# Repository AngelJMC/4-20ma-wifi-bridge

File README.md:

# 4-20ma-wifi-bridge
IoT device to provide communication between 4-20mA sensors and cloud services. Powered by an ESP32, it allows a wireless connection via WIFI, the communication with the server is done through the MQTT protocol. The device has a user-friendly web configuration interface, which allows to manage the wifi connection, the connection with the MQTT broker as well as the calibration of the 4-20mA acquisition system. 

## Features
### Hardware
 * 5-24v Power supply.
 * 1 Input 4-20 mA.
 * 2 Relays to control loads up to 1A at 24DVC or 0.5A at 125VAC.
 * WIFI 802.11 b/g/n (2.4 GHz), up to 150 Mbps.

## Get the source code
Download repository and update submodules:

```
$ git clone https://github.com/AngelJMC/4-20ma-wifi-bridge.git
```

### Directory Structure

    .
    ├── docs          # Documentation files
    ├── firmware      # FW source code (Visual Studio Code)
    ├── hardware      # HW design files (Kicad)

## Firmware

If you want to modify the source code or program your devices, it is highly recommended to use Visual Studio Code and the Platformio plugin. Just open the "firmware" directory with Visual Studio Code and the whole project will be ready for use.

### Load firmware 

 1. Build and Upload Filesystem Image.
 2. Build and Upload program code.

## Configuration Process

 1. Build and Upload Filesystem Image to your ESP32
 2. Build and Upload program code.
 3. Connect mobile or PC with hotspot: Logger_4-20mA_XXXX. Password: Kmf5cyJUWw
 4. Go to web browser and hit 192.168.4.1. Use the credential supervisor/fEVcCQxig to enter.
 5. Go to Network section and scan for your wifi network, write password and static network configuration if you want, hit apply.
 6. Go to Service section give necessary server credential for MQTT and set the pub/sub topic names.
 7. Go to Other section if you need calibrate the 4-20mA acquisition electronic.

## Configuration Web

## Library Used

* ESp32_arduino :- https://github.com/espressif/arduino-esp32
* ESPAsyncWebServer:- https://github.com/me-no-dev/ESPAsyncWebServer
* AsyncTCP:- https://github.com/me-no-dev/AsyncTCP
* esp32 SPIFF File system :- https://github.com/me-no-dev/arduino-esp32fs-plugin

The configuration web page is based on the work of @futechiot https://github.com/futechiot/Configuration-webpage-esp32

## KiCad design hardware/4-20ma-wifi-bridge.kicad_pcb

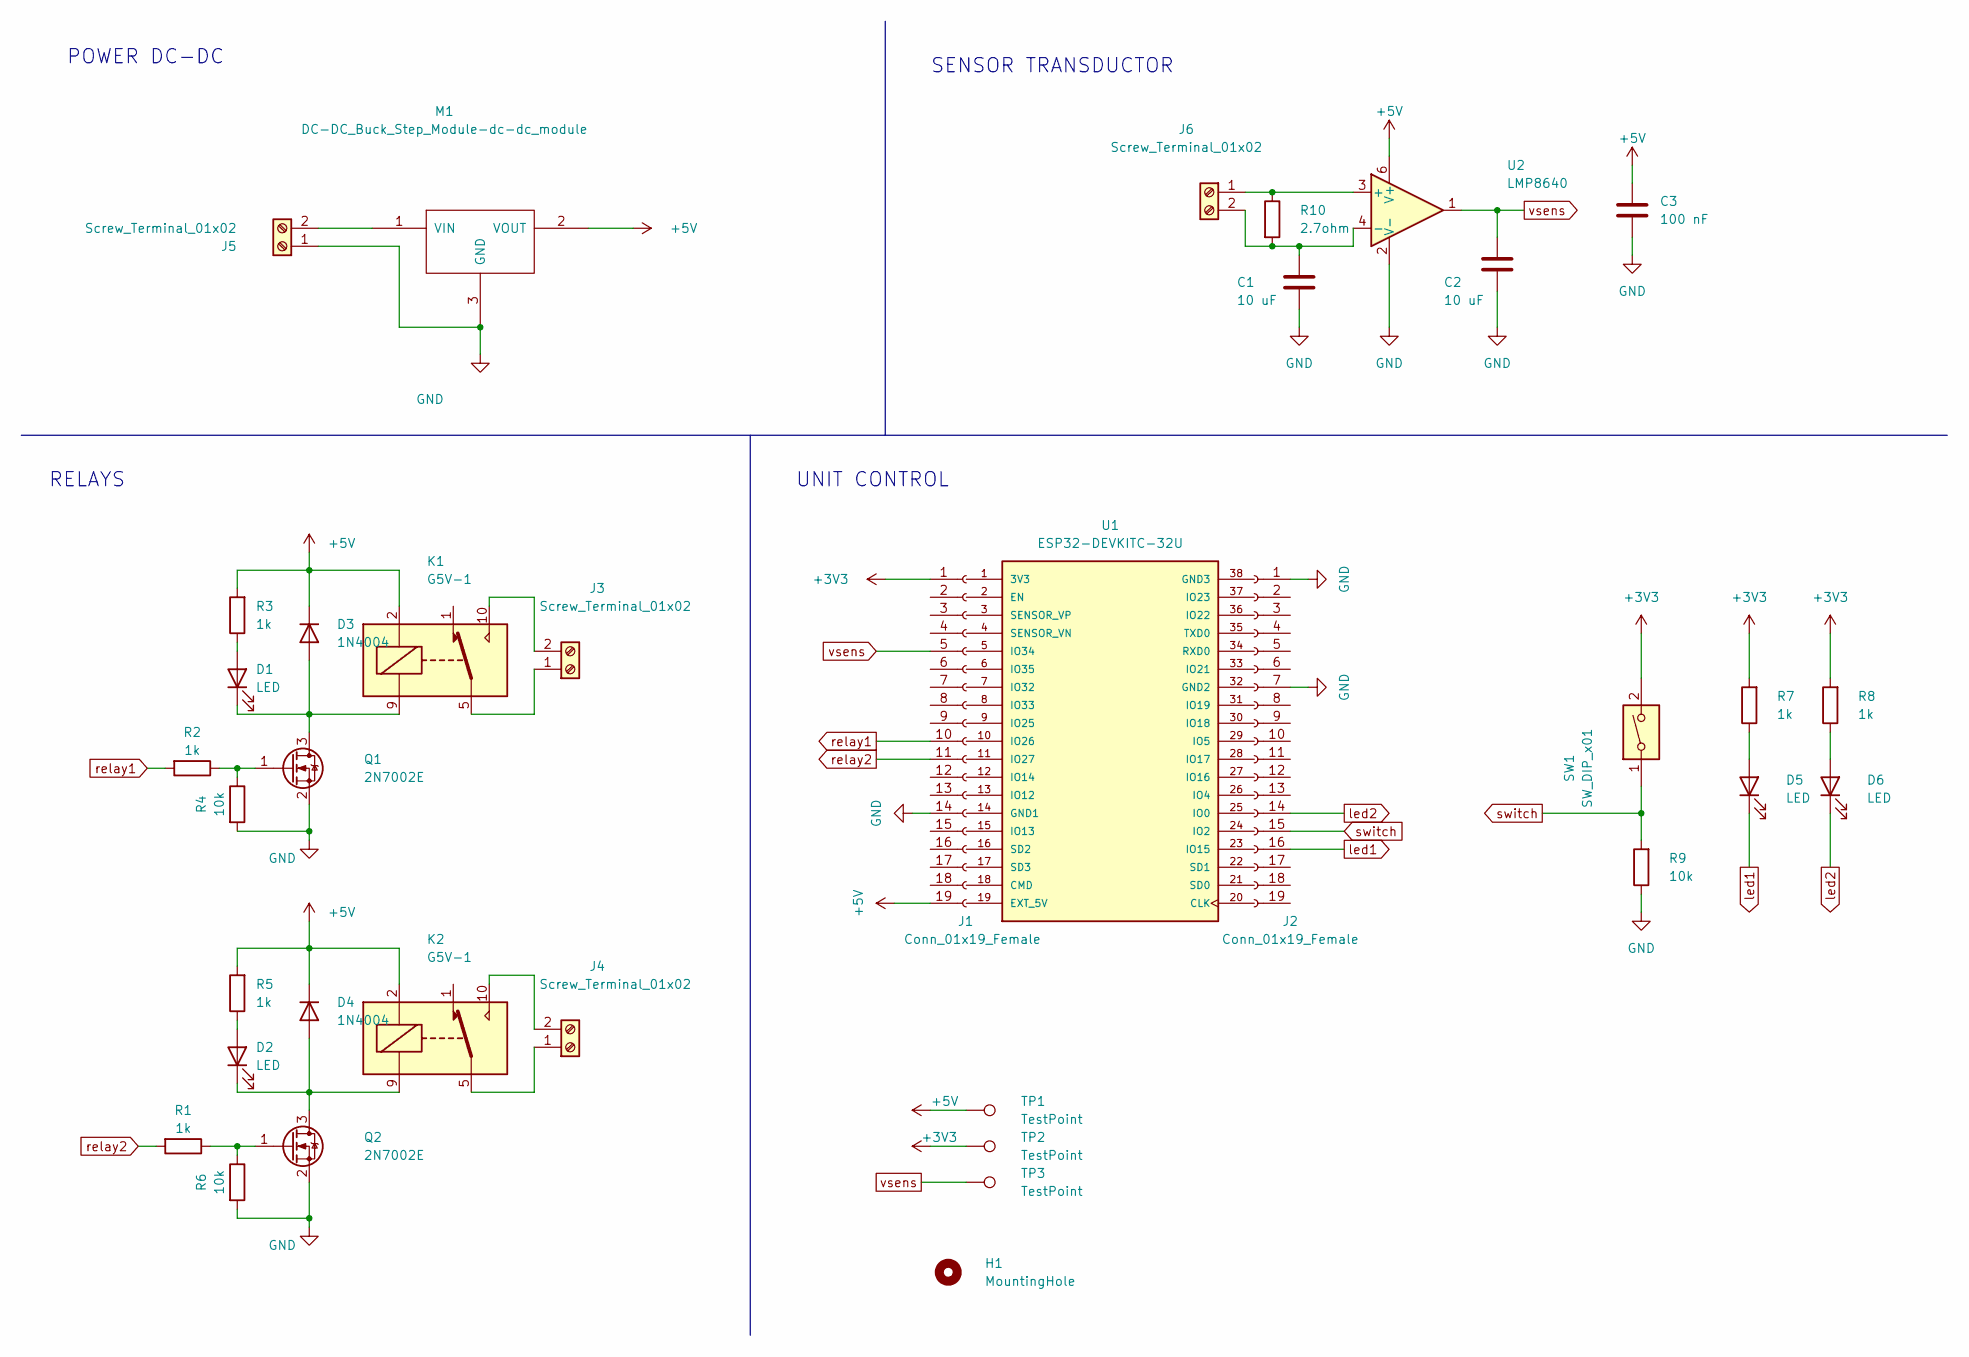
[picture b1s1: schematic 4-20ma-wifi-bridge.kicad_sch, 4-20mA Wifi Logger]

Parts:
C1, C2: 10 uF; C_0805_2012Metric_Pad1.18x1.45mm_HandSolder
C3: 100 nF; C_0805_2012Metric_Pad1.18x1.45mm_HandSolder
D1, D2: LED; LED_D3.0mm_FlatTop
D3, D4: 1N4004; D_SMA
D5, D6: LED; LED_D1.8mm_W1.8mm_H2.4mm_Horizontal_O1.27mm_Z1.6mm
H1: MountingHole; MountingHole_2.7mm_M2.5_ISO7380_Pad
J1, J2: Conn_01x19_Female; PinSocket_1x19_P2.54mm_Vertical
J3, J4, J5, J6: Screw_Terminal_01x02; TerminalBlock__1x02_P5.00mm_90Degree
K1, K2: G5V-1; Relay_SPDT_Omron_G5V-1
M1: DC-DC_Buck_Step_Module-dc-dc_module; DC-DC_Buck_Step_Module
Q1, Q2: 2N7002E; SOT-23
R1, R2, R3, R5, R7, R8: 1k; R_0805_2012Metric_Pad1.20x1.40mm_HandSolder
R4, R6, R9: 10k; R_0805_2012Metric_Pad1.20x1.40mm_HandSolder
R10: 2.7ohm; R_2512_6332Metric_Pad1.40x3.35mm_HandSolder
SW1: SW_DIP_x01; SW_Tactile_SPST_Angled_PTS645Vx58-2LFS
TP1, TP2, TP3: TestPoint; TestPoint_Pad_D1.0mm
U1: ESP32-DEVKITC-32U; MODULE_ESP32-DEVKITC-32U; PARTREV N/A
U2: LMP8640; SOT-23-6

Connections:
+3V3: J1.1, R7.2, R8.2, SW1.2, TP2.1
+5V: C3.1, D3.1 (K), D4.1 (K), J1.19, K1.2, K2.2, M1.2 (VOUT), R3.2, R5.2, TP1.1, U2.6 (V+)
GND: C1.2, C2.2, C3.2, J1.14, J2.1, J2.7, J5.1, M1.3 (GND), Q1.2 (S), Q2.2 (S), R4.2, R6.2, R9.1, U2.2 (V-)
unnamed: C1.1, J6.2, R10.2, U2.4 (-)
unnamed: D1.1 (K), D3.2 (A), K1.9, Q1.3 (D)
unnamed: D1.2 (A), R3.1
unnamed: D2.1 (K), D4.2 (A), K2.9, Q2.3 (D)
unnamed: D2.2 (A), R5.1
unnamed: D5.2 (A), R7.1
unnamed: D6.2 (A), R8.1
unnamed: J3.1, K1.5, K1.6
unnamed: J3.2, K1.10
unnamed: J4.1, K2.5, K2.6
unnamed: J4.2, K2.10
unnamed: J5.2, M1.1 (VIN)
unnamed: J6.1, R10.1, U2.3 (+)
unnamed: Q1.1 (G), R2.1, R4.1
unnamed: Q2.1 (G), R1.1, R6.1
led1: D5.1 (K), J2.16
led2: D6.1 (K), J2.14
relay1: J1.10, R2.2
relay2: J1.11, R1.2
switch: J2.15, R9.2, SW1.1
vsens: C2.1, J1.5, TP3.1, U2.1

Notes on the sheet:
RELAYS
UNIT CONTROL
SENSOR TRANSDUCTOR
POWER DC-DC

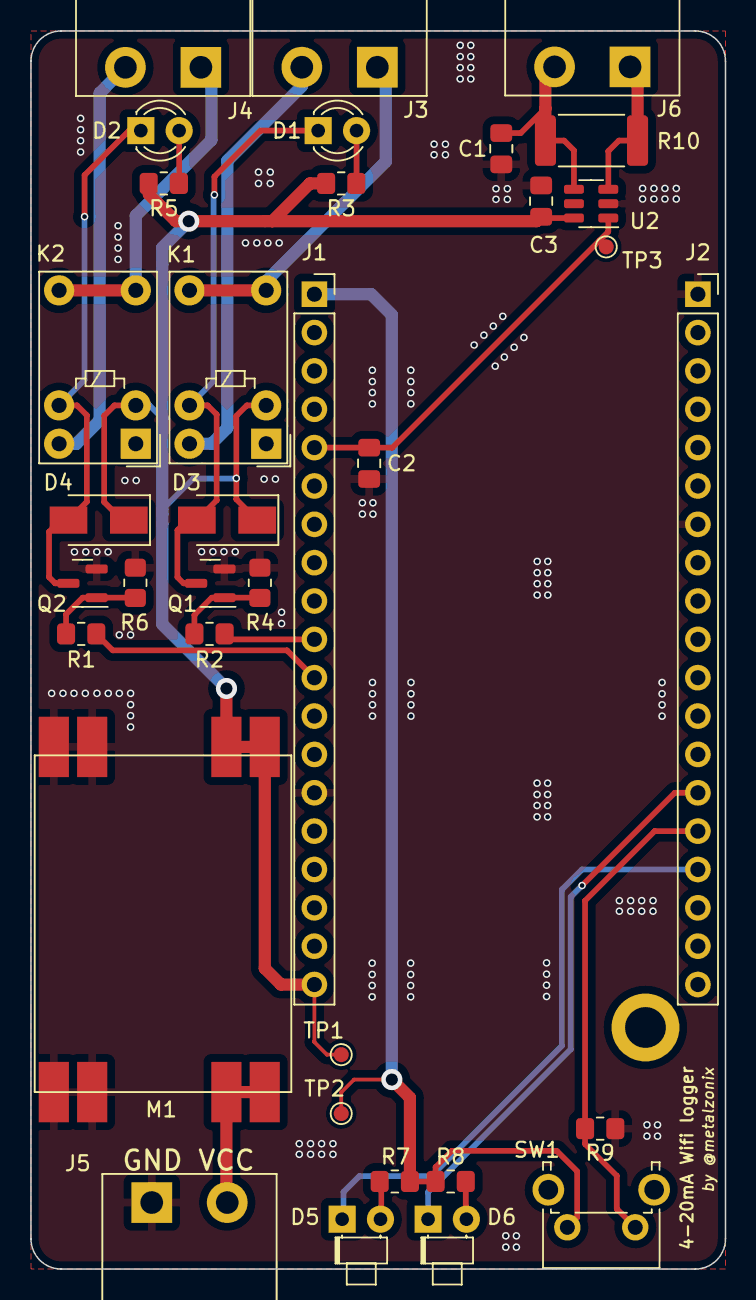
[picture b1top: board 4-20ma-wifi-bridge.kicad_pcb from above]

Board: 2 copper layers, 46.0 x 82.0 mm, 36 parts (0 on the bottom side), 24 nets.

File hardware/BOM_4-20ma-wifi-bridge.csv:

Id,Designator,Quantity,Supplier and ref,Value,Package
1,R10,1,ERJ1TRQF2R7U,2.7ohm,R_2512_6332Metric_Pad1.40x3.35mm_HandSolder
2,"R5,R3,R1,R2,R7,R8",6,ERJ6GEYJ102V,1k,R_0805_2012Metric_Pad1.20x1.40mm_HandSolder
3,"R6,R4,R9",3,ERJ6GEY J103V,10k,R_0805_2012Metric_Pad1.20x1.40mm_HandSolder
4,"C1,C2",2,CL21B106KPQNNNE,10 uF,C_0805_2012Metric_Pad1.18x1.45mm_HandSolder
5,C3,1,CL21B104KCFNNNE,100 nF,C_0805_2012Metric_Pad1.18x1.45mm_HandSolder
6,D5,1,L-204SRD,LED RED,LED_D1.8mm_W1.8mm_H2.4mm_Horizontal_O1.27mm_Z1.6mm
7,D6,1,L-204GD,LED GREEN,LED_D1.8mm_W1.8mm_H2.4mm_Horizontal_O1.27mm_Z1.6mm
8,"D2,D1",2,204-10SURD/S530-A3-L,LED,LED_D3.0mm_FlatTop
9,"D4,D3",2,1N4004,1N4004,D_SMA
10,"Q2,Q1",2,2N7002E,2N7002E,SOT-23
11,U1,1,ESP32-WROOM-32U,ESP32-DevKitC V4,MODULE_ESP32-DEVKITC-32U
12,U2,1,LMP8640MK-F/NOPB,LMP8640,SOT-23-6
13,"K2,K1",2,G5V-1-DC5,G5V-1,Relay_SPDT_Omron_G5V-1
14,"J2,J1",2,C319202,Conn_01x19_Female,PinSocket_1x19_P2.54mm_Vertical
15,"J4,J3,J5,J6",4,KF2EDGRC-5.0-2P,KF2EDGRC-5.0-2P,TerminalBlock__1x02_P5.00mm_90Degree
16,"J4,J3,J5,J6",4,KF2EDGK-5.0-2P,KF2EDGK-5.0-2P,TerminalBlock__1x02_P5.00mm_90Degree Female
17,SW1,1,PTS645VH582LFS,SW_DIP_x01,SW_Tactile_SPST_Angled_PTS645Vx58-2LFS
18,M1,1,,DC-DC_Buck_Step_Module-dc-dc_module,DC-DC_Buck_Step_Module
19,,1,,"Antena WiFi de 2,4 GHz y 3dBi, ","Antena WiFi de 2,4 GHz y 3dBi, "

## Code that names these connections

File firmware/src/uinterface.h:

/*
    Project: <https://github.com/AngelJMC/4-20ma-wifi-bridge>   
    Copyright (c) 2022 Angel Maldonado <angelgesus@gmail.com>. 
    Licensed under the MIT License: <http://opensource.org/licenses/MIT>.
    SPDX-License-Identifier: MIT 
*/

#ifndef __U_INTERFACE__
#define __U_INTERFACE__

#include "stdint.h"

#define LED_OFF 0x1
#define LED_ON 0x0

enum {  
    RELAY1 = 26, 
    RELAY2 = 27,
    SENS   = 34,
    LED1   = 0,
    LED2   = 15,
    SWITCH = 2 
};

/*Led status modes*/
enum modes {
    OFF = 0,
    BLINK = 1,
    ON = 2
};

/**
 * @brief Initialize the leds controls */
void interface_init( void );

/**
 * @brief Set the state of the led used as Mode indicator (RED)
 * @param mode, the state of the led: OFF, BLINK, ON */
void interface_setMode( enum modes mode );

/**
 * @brief Set the state of the led used as State indicator (GREEN)
 * @param mode, the state of the led: OFF, BLINK, ON */
void interface_setState( enum modes mode );

/**
 * @brief This function reads some ADC acquisitions and return the filtered value. */
int16_t getadcValue( void );

/**
 * @brief This function does a factory reset of the device. */
void factoryreset( void );

#endif //__U_INTERFACE__ 

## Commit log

2021-12-26 Wokr around pcb design
2022-01-18 Added kicad design files
2022-01-19 First version of webserver
2022-01-19 Improving code readability
2022-01-29 Work around service data page and the json parsing
2022-02-01 Improved communication front/back-end. Improved architecture
2022-02-06 Added NTP configuration from webserver. Improved error checking
2022-02-06 Publish timestamp and adc reading
2022-02-06 Fix minor issues
2022-02-13 Improved stability when loading the configuration website
2022-02-15 Improved debug functions
2022-02-19 Implementation of led control and switch to enter in configuration mode.
2022-02-20 Implemented feature to calibrate sensor from the web pannel.
2022-02-20 Added interface code
2022-03-03 Fixed bug related to the static network configuration. Encode URI component
2022-03-04 Improve calibration default config
2022-03-08 Minor changes. Improved modularity
2022-03-13 Fix minor bug and improve documentation
2022-03-13 Submodule deleted
2022-03-13 Added source of AsyncTCP library
2022-03-13 Added source of ESPAsyncWebServer library
2022-03-13 Update gitignore
2022-03-13 Update async event queue to avoid crash when web files are servered
2022-03-13 Minor changes, bug fixing related to the mac address byte intepretation.
2022-03-15 Updated schematic and board to fix some erros
2022-03-21 Added mqtt client test
2022-03-21 Added BOM and other vs project files
2022-03-21 Updated hardware design files
2022-03-21 Updated license
2022-03-22 Upload documentation
2022-05-05 Changed configuration mode and AP behaviour
    Now only enable/disable access point and web when the user press the
    config button.
2022-05-05 Check MQTT connection status, attempt to reconnect if there is a problem.
2022-05-05 Send json with the status indo after any topic is received.
2022-05-06 Fix minor issue related to configuration mode
